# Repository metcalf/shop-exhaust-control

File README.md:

# Shop Exhaust Fan Controller

An ESP32 (ESP-IDF) controller for the woodshop exhaust fan. It runs the fan from particulate sensing and dust collector activity, with local physical controls and Home Assistant reporting. This is the pilot for a Claude-led design process; a dust collector controller follows it.

## Getting started
1. `git init`, then commit this skeleton.
2. Fill in `docs/site-survey.md` (★ items at minimum) and drop photos in `docs/site/`.
3. Answer what you can in `docs/open-questions.md`.
4. Open Claude Code in this directory and say: *"Read CLAUDE.md and STATE.md, then review the site survey and start phase 1."*

Claude follows `CLAUDE.md`: it keeps `STATE.md` current, batches questions, and stops for your approval at each gate (G1–G5).

## Layout
| Path | Purpose |
|------|---------|
| `CLAUDE.md` | Operating instructions for Claude (process, gates, safety rules, conventions) |
| `STATE.md` | Current phase, next actions, blockers |
| `docs/context.md` | Kickoff brief: design thinking already done |
| `docs/site-survey.md` | Your inputs about the shop, fan and preferences |
| `docs/requirements.md` | Requirements with IDs and acceptance criteria |
| `docs/interfaces.md` | I/O, Home Assistant entities, and the shared `DC_RUNNING` interface |
| `docs/decisions.md` | Decision log and gate approvals |
| `docs/open-questions.md` | Batched questions with default assumptions |
| `docs/process-notes.md` | Lessons for the DC project |
| `.claude/agents/` | Subagent definitions: `reviewer` (independent gate reviews), `sourcing` (parts research) |
| `bom.csv` | Bill of materials |
| `firmware/`, `pcb/`, `electrical/`, `mech/`, `reviews/`, `sourcing/` | Created as phases begin |

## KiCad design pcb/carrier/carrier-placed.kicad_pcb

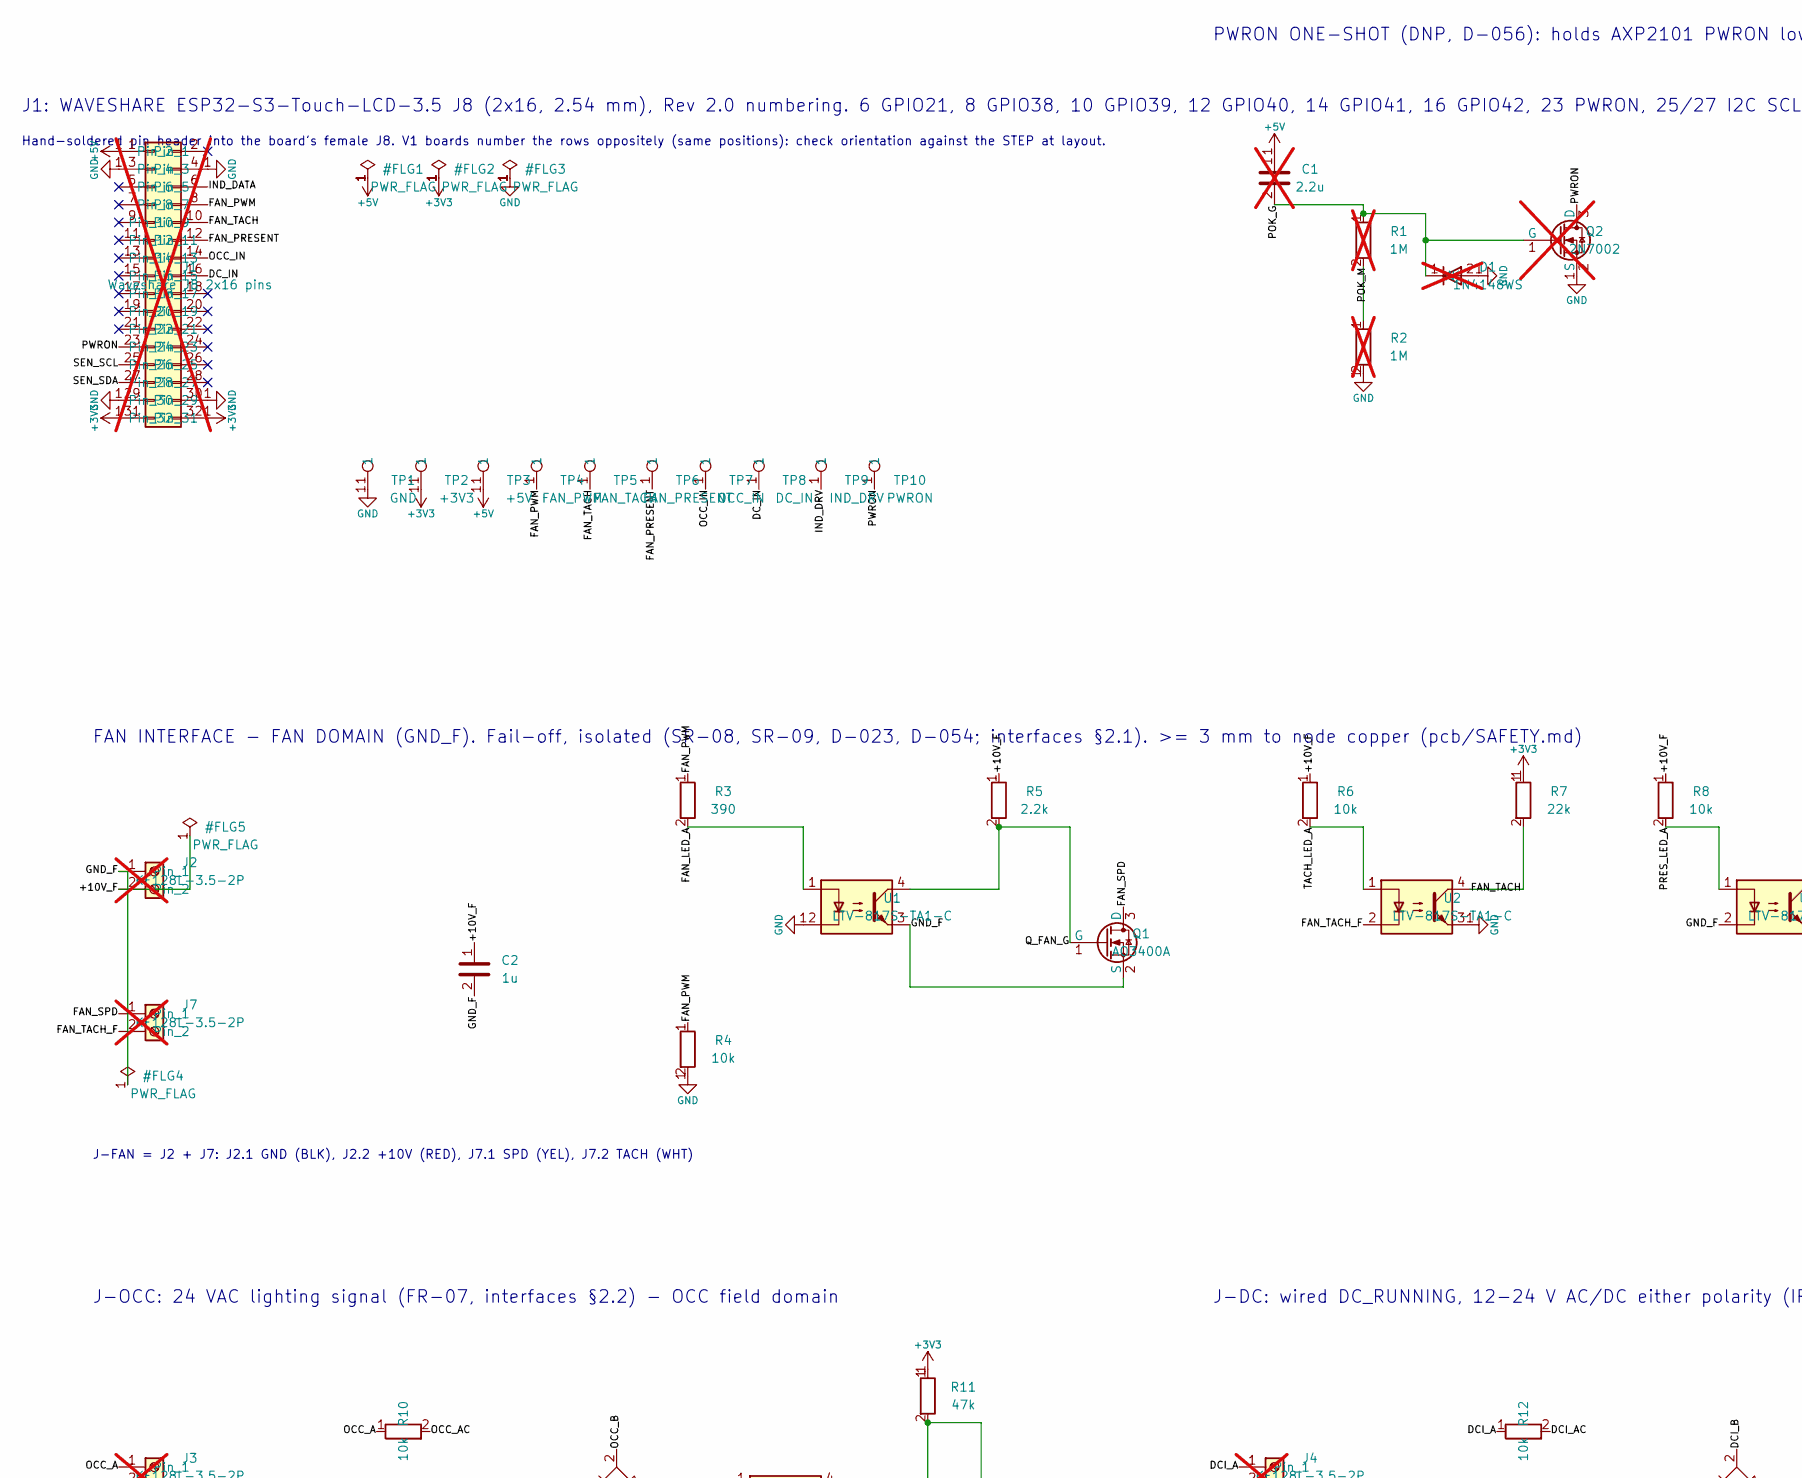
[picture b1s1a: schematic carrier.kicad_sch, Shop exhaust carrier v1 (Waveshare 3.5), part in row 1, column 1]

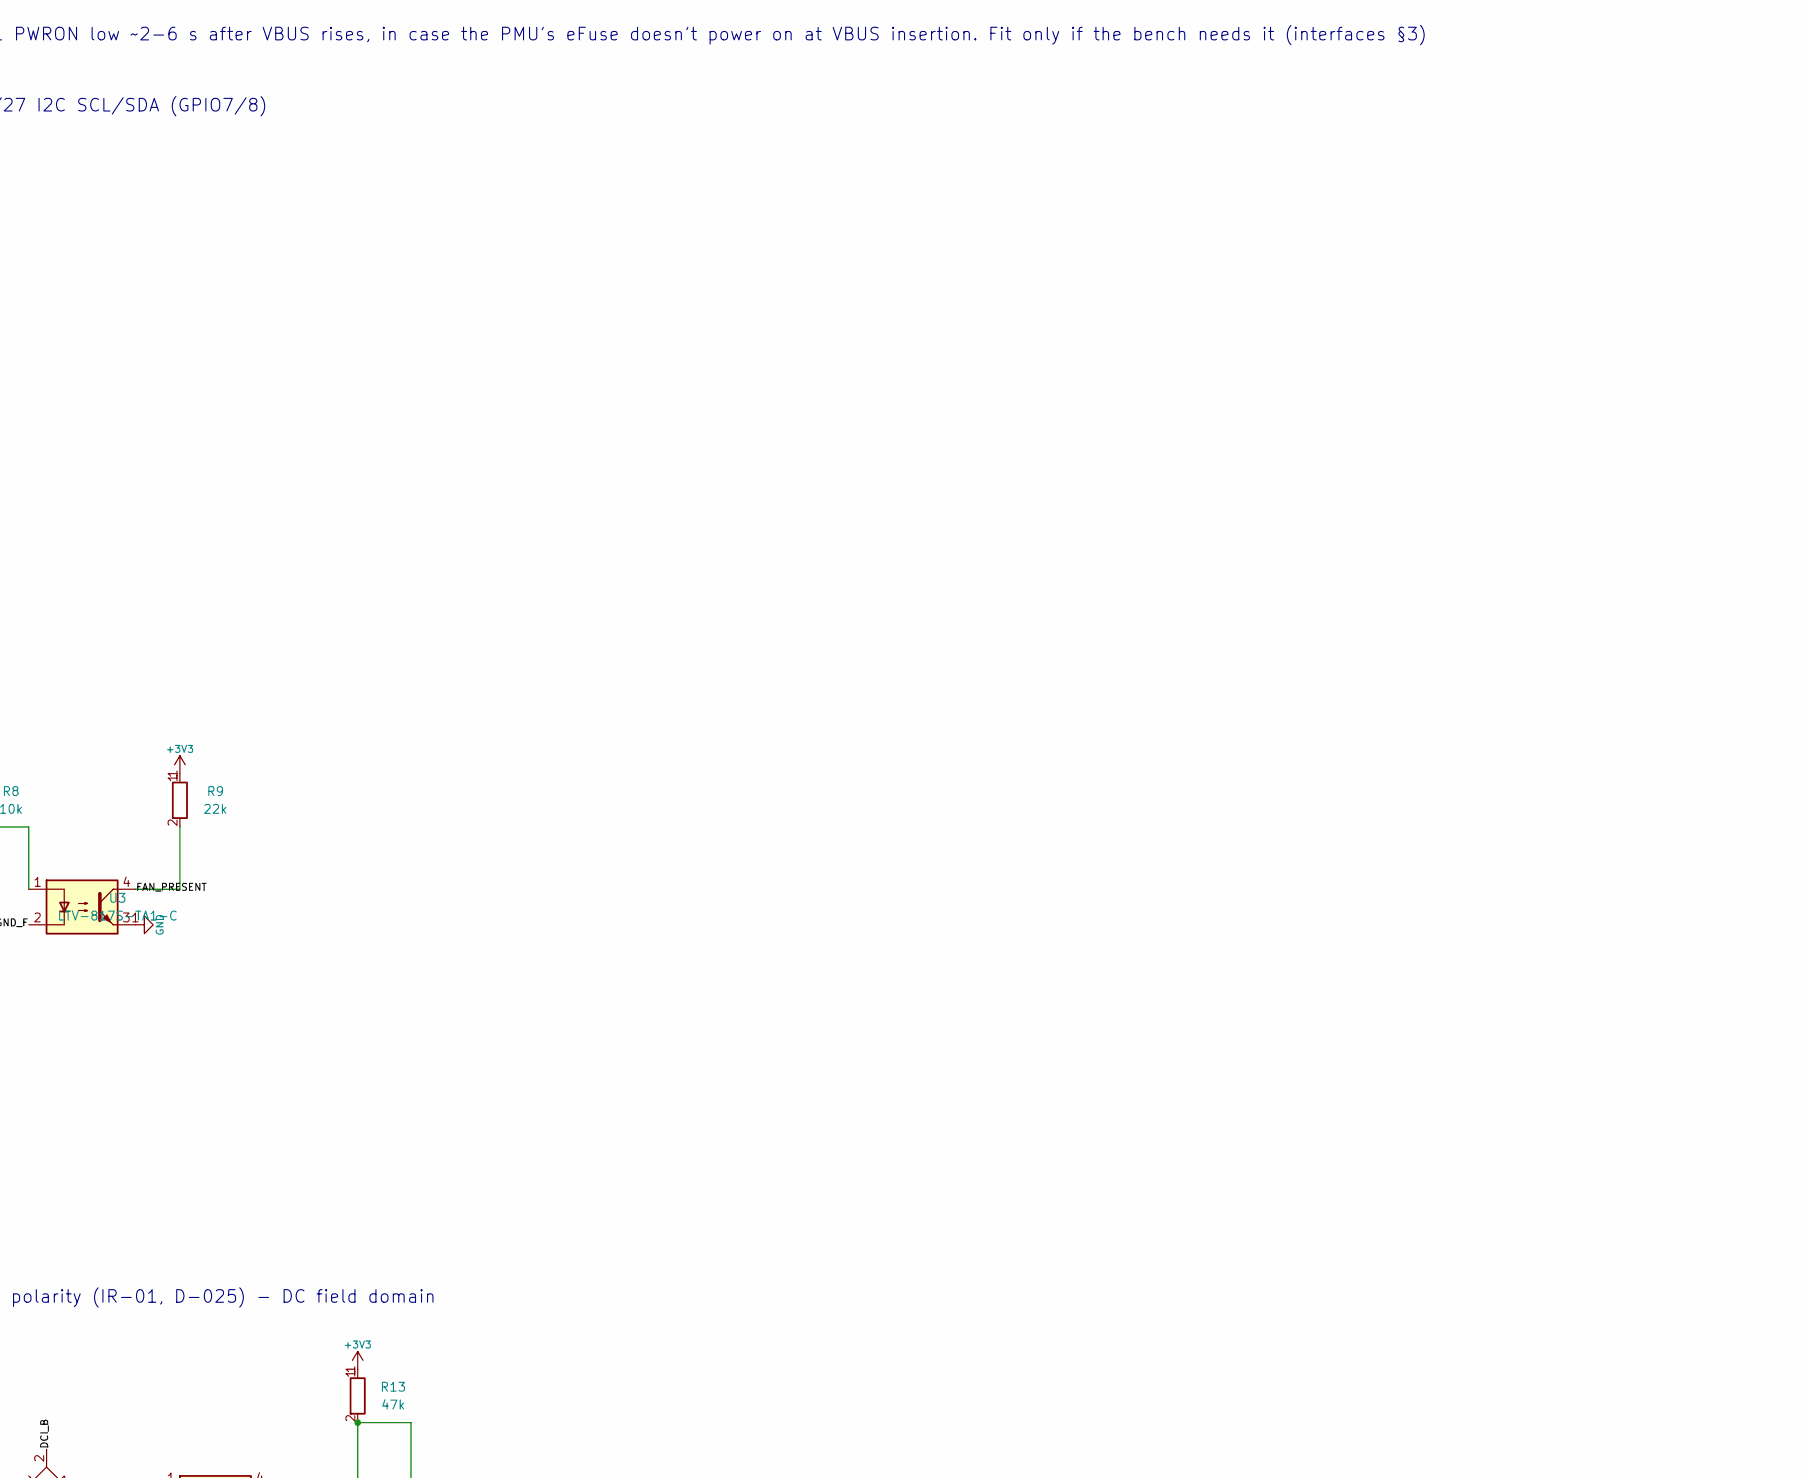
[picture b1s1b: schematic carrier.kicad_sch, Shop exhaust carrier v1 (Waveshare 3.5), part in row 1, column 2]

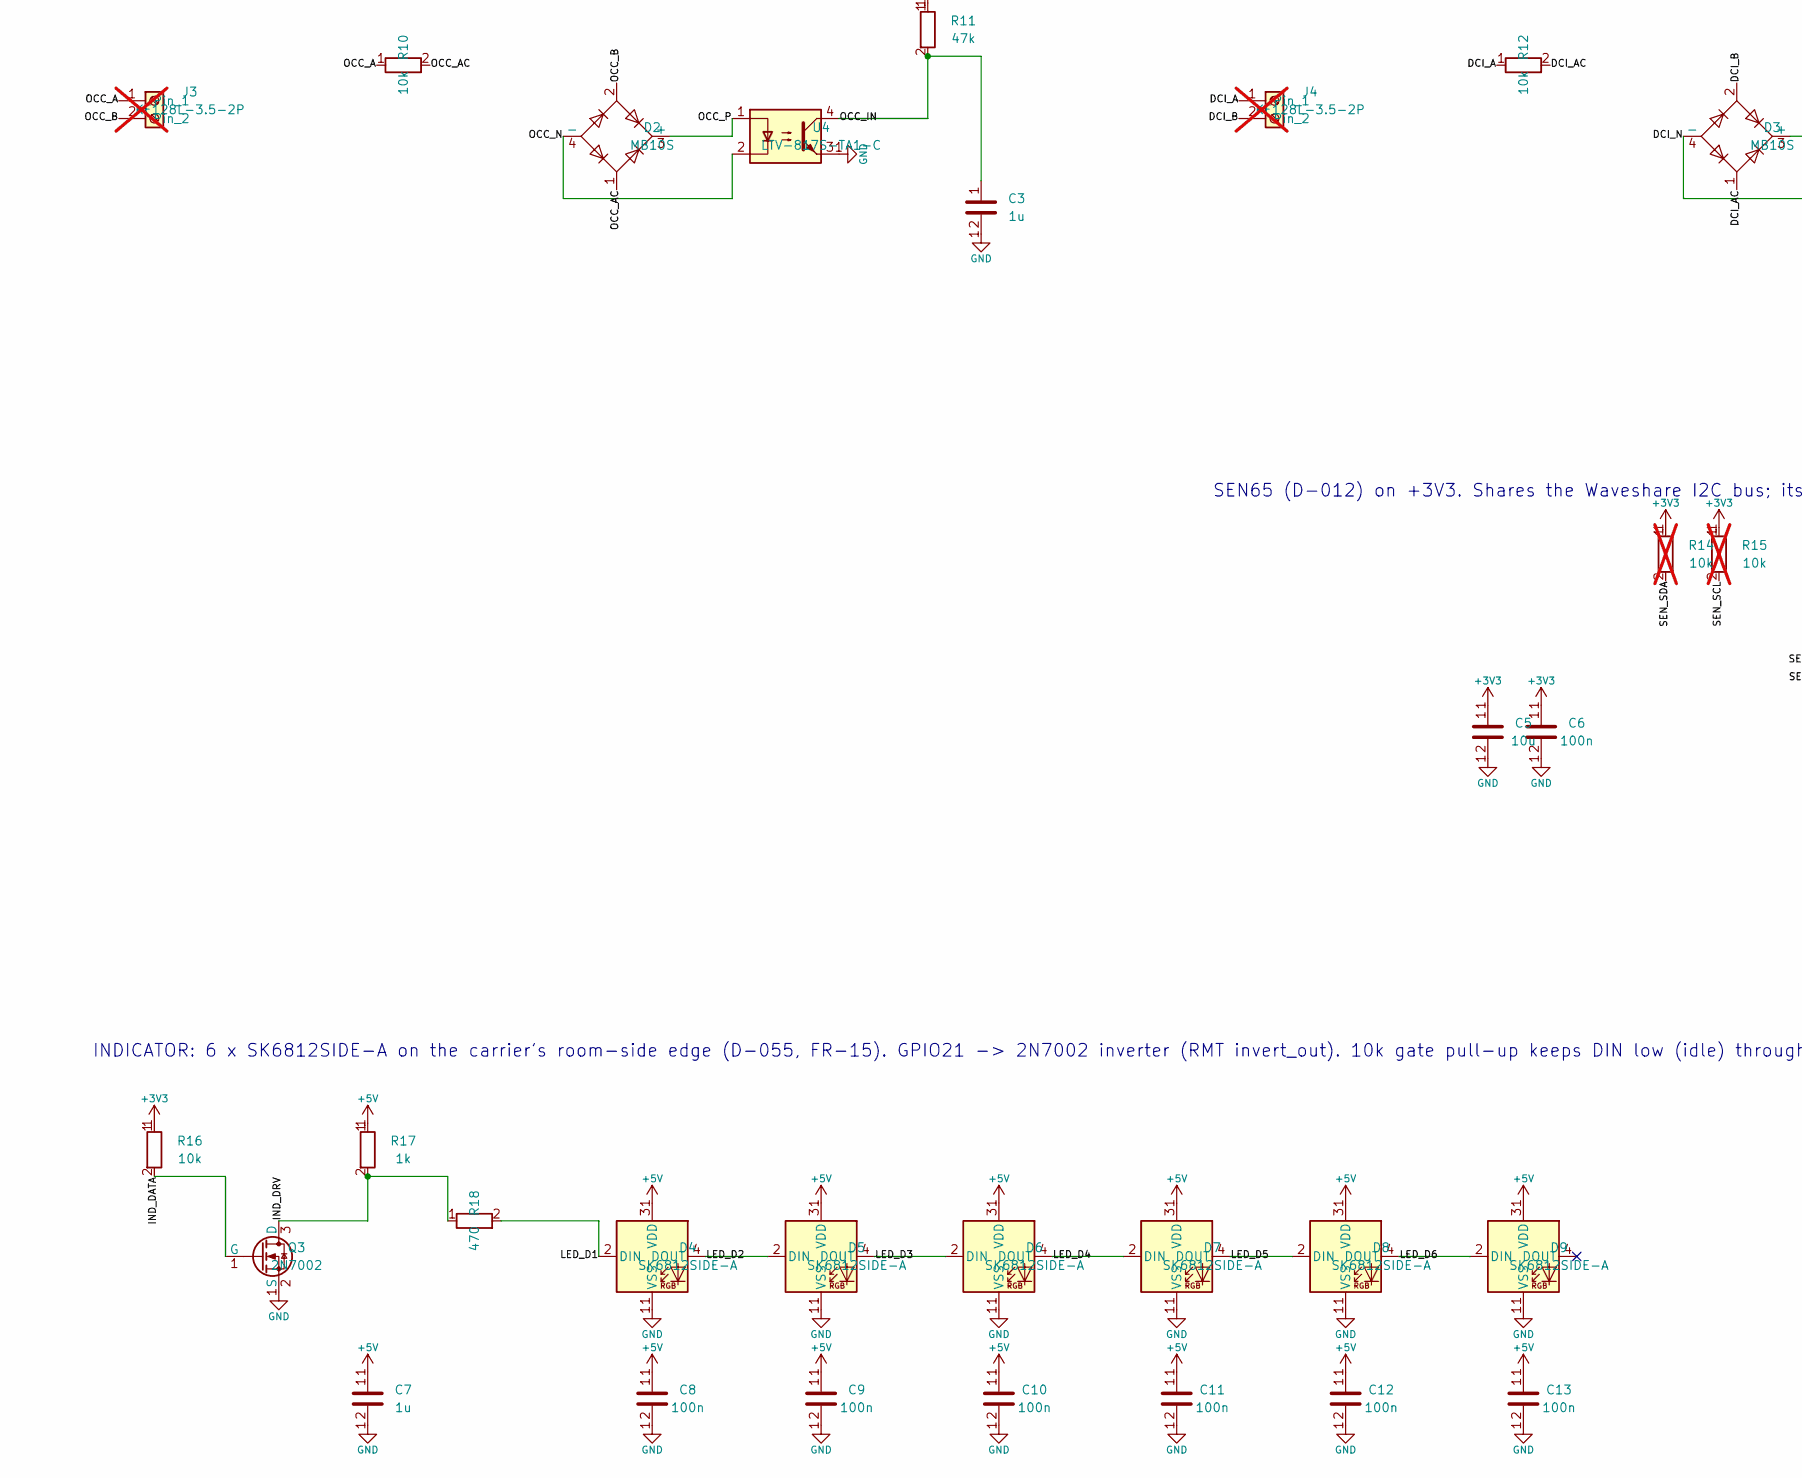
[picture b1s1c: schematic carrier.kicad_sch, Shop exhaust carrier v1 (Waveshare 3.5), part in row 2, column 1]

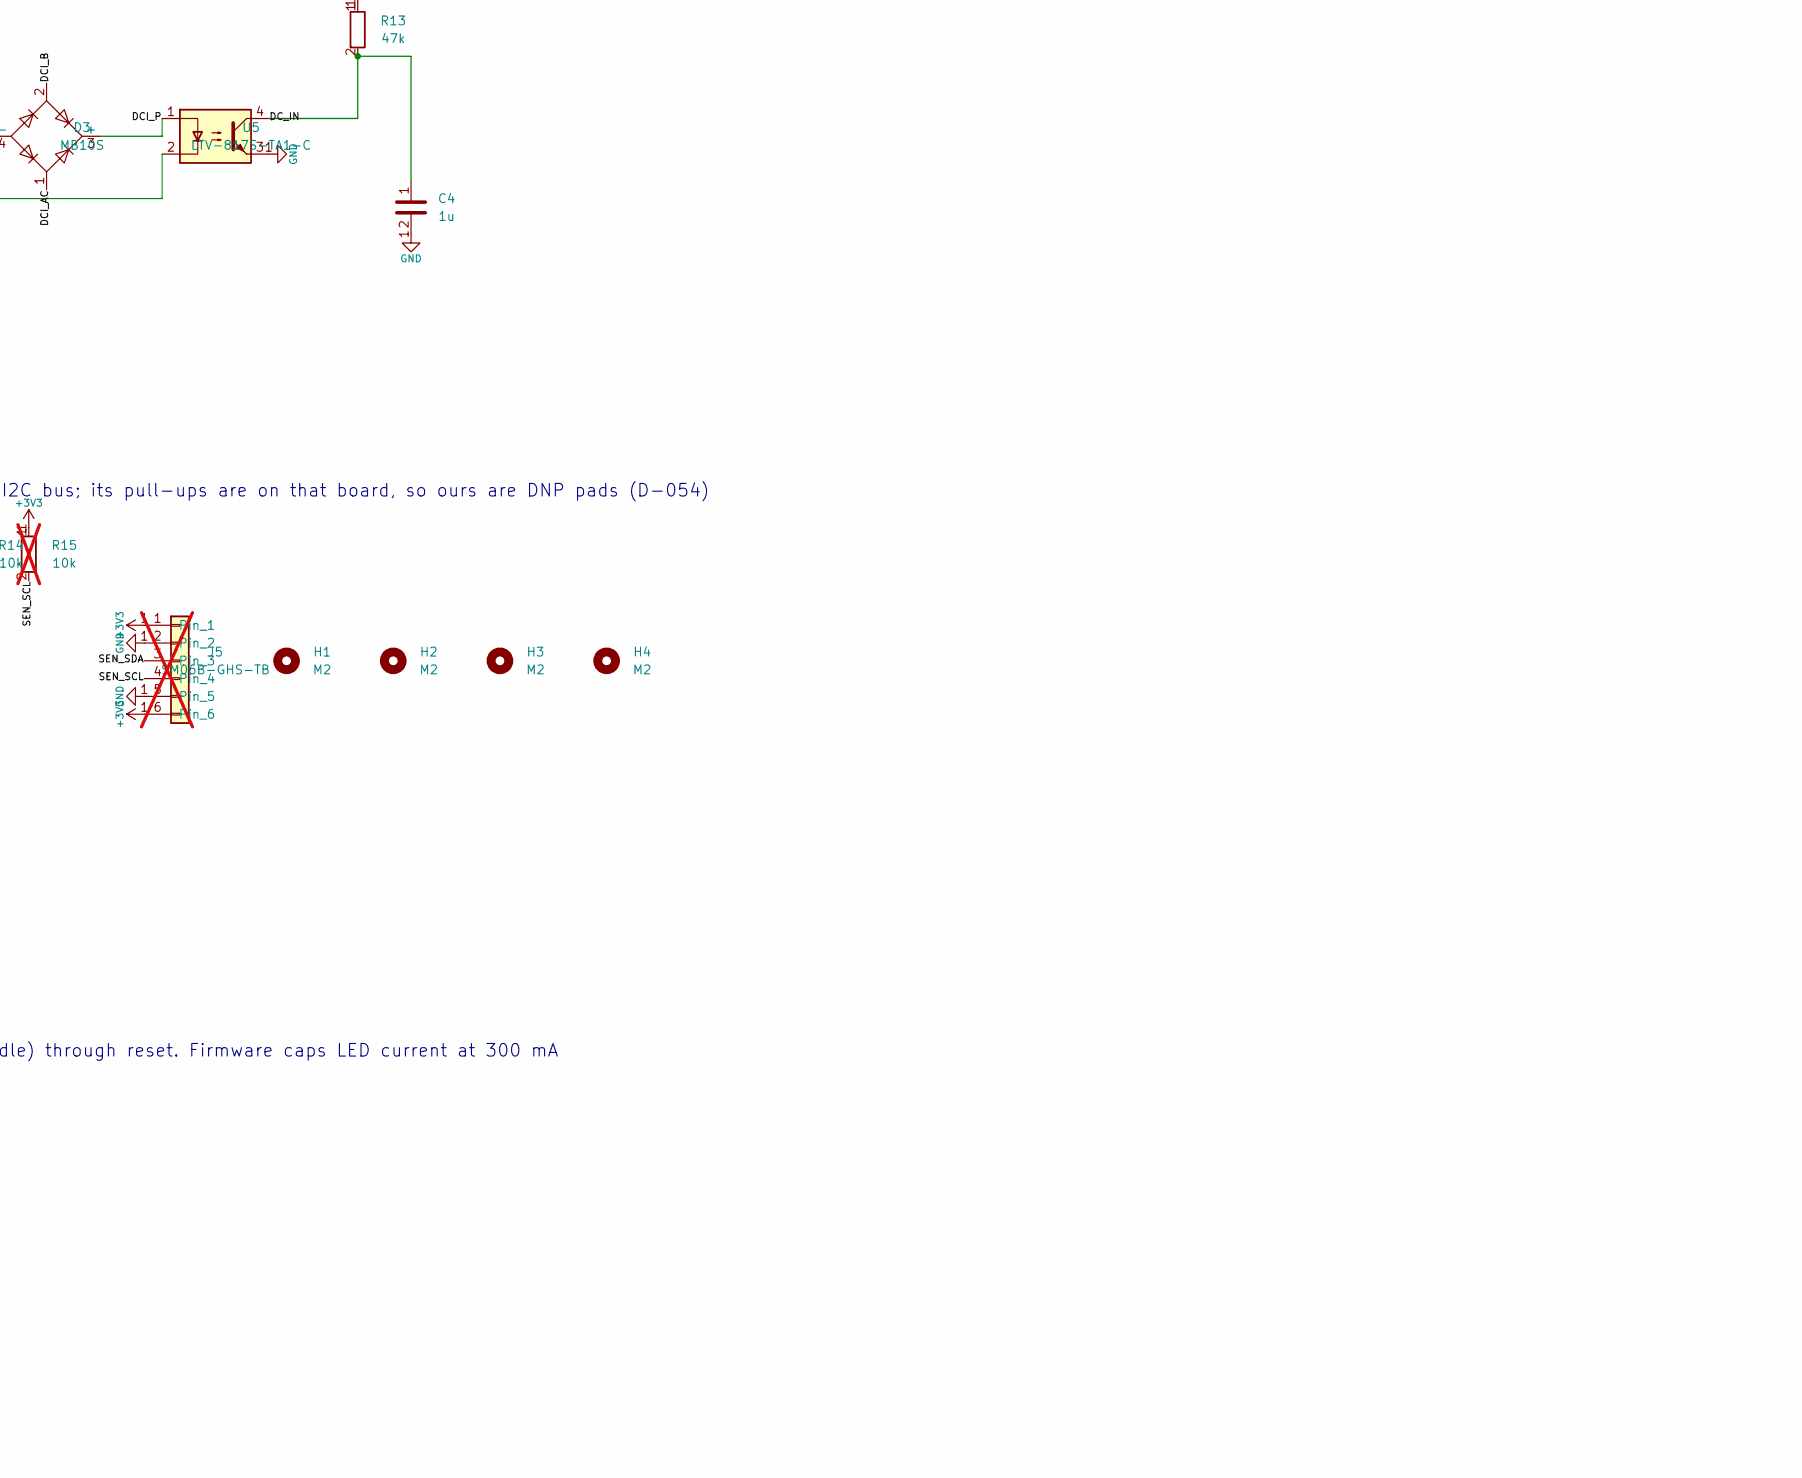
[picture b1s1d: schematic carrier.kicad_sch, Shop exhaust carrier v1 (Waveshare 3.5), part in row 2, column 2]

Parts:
C1: 2.2u; C_0603_1608Metric; not fitted
C2, C3, C4, C7: 1u; C_0603_1608Metric
C5: 10u; C_0805_2012Metric
C6, C8, C9, C10, C11, C12, C13: 100n; C_0603_1608Metric
D1: 1N4148WS; D_SOD-323; LCSC C2128; not fitted
D2, D3: MB10S; Bridge_MBS_MB10S; LCSC C2488
D4, D5, D6, D7, D8, D9: SK6812SIDE-A; LED_SK6812SIDE-A_4.0x1.6mm; LCSC C5378721
H1, H2, H3, H4: M2; MountingHole_2.2mm_M2
J1: Waveshare J8 2x16 pins; PinHeader_2x16_P2.54mm_Vertical; not fitted
J2, J3, J4, J7: KF128L-3.5-2P; TerminalBlock_KF128L-3.5-2P; LCSC C474930; not fitted
J5: SM06B-GHS-TB; JST_GH_SM06B-GHS-TB_1x06-1MP_P1.25mm_Horizontal; LCSC C133065; not fitted
Q1: AO3400A; SOT-23; LCSC C20917
Q2: 2N7002; SOT-23; LCSC C8545; not fitted
Q3: 2N7002; SOT-23; LCSC C8545
R1, R2: 1M; R_0603_1608Metric; not fitted
R3: 390; R_0603_1608Metric
R4, R6, R8, R16: 10k; R_0603_1608Metric
R5: 2.2k; R_0603_1608Metric
R7, R9: 22k; R_0603_1608Metric
R10, R12: 10k; R_1206_3216Metric
R11, R13: 47k; R_0603_1608Metric
R14, R15: 10k; R_0603_1608Metric; not fitted
R17: 1k; R_0603_1608Metric
R18: 470; R_0603_1608Metric
TP1: GND; TestPoint_Pad_D1.5mm
TP2: +3V3; TestPoint_Pad_D1.5mm
TP3: +5V; TestPoint_Pad_D1.5mm
TP4: FAN_PWM; TestPoint_Pad_D1.5mm
TP5: FAN_TACH; TestPoint_Pad_D1.5mm
TP6: FAN_PRESENT; TestPoint_Pad_D1.5mm
TP7: OCC_IN; TestPoint_Pad_D1.5mm
TP8: DC_IN; TestPoint_Pad_D1.5mm
TP9: IND_DRV; TestPoint_Pad_D1.5mm
TP10: PWRON; TestPoint_Pad_D1.5mm
U1, U2, U3, U4, U5: LTV-817S-TA1-C; SOP-4_LTV-817S_LS10.3; LCSC C109227

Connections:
+3V3: C5.1, C6.1, J1.31, J1.32, J5.1, J5.6, R7.1, R9.1, R11.1, R13.1, R14.1, R15.1, R16.1, TP2.1
+5V: C1.1, C7.1, C8.1, C9.1, C10.1, C11.1, C12.1, C13.1, D4.3 (VDD), D5.3 (VDD), D6.3 (VDD), D7.3 (VDD), D8.3 (VDD), D9.3 (VDD), J1.1, R17.1, TP3.1
/+10V_F: C2.1, J2.2, R5.1, R6.1, R8.1
/DCI_A: J4.1, R12.1
/DCI_AC: D3.1, R12.2
/DCI_B: D3.2, J4.2
/DCI_N: D3.4 (-), U5.2
/DCI_P: D3.3 (+), U5.1
/DC_IN: C4.1, J1.16, R13.2, TP8.1, U5.4
/FAN_LED_A: R3.2, U1.1
/FAN_PRESENT: J1.12, R9.2, TP6.1, U3.4
/FAN_PWM: J1.8, R3.1, R4.1, TP4.1
/FAN_SPD: J7.1, Q1.3 (D)
/FAN_TACH: J1.10, R7.2, TP5.1, U2.4
/FAN_TACH_F: J7.2, U2.2
/GND_F: C2.2, J2.1, Q1.2 (S), U1.3, U3.2
/IND_DATA: J1.6, Q3.1 (G), R16.2
/IND_DRV: Q3.3 (D), R17.2, R18.1, TP9.1
/LED_D1: D4.2 (DIN), R18.2
/LED_D2: D4.4 (DOUT), D5.2 (DIN)
/LED_D3: D5.4 (DOUT), D6.2 (DIN)
/LED_D4: D6.4 (DOUT), D7.2 (DIN)
/LED_D5: D7.4 (DOUT), D8.2 (DIN)
/LED_D6: D8.4 (DOUT), D9.2 (DIN)
/OCC_A: J3.1, R10.1
/OCC_AC: D2.1, R10.2
/OCC_B: D2.2, J3.2
/OCC_IN: C3.1, J1.14, R11.2, TP7.1, U4.4
/OCC_N: D2.4 (-), U4.2
/OCC_P: D2.3 (+), U4.1
/POK_G: C1.2, D1.1 (K), Q2.1 (G), R1.1
/POK_M: R1.2, R2.1
/PRES_LED_A: R8.2, U3.1
/PWRON: J1.23, Q2.3 (D), TP10.1
/Q_FAN_G: Q1.1 (G), R5.2, U1.4
/SEN_SCL: J1.25, J5.4, R15.2
/SEN_SDA: J1.27, J5.3, R14.2
/TACH_LED_A: R6.2, U2.1
GND: C3.2, C4.2, C5.2, C6.2, C7.2, C8.2, C9.2, C10.2, C11.2, C12.2, C13.2, D1.2 (A), D4.1 (VSS), D5.1 (VSS), D6.1 (VSS), D7.1 (VSS), D8.1 (VSS), D9.1 (VSS), J1.3, J1.4, J1.29, J1.30, J5.2, J5.5, Q2.2 (S), Q3.2 (S), R2.2, R4.2, TP1.1, U1.2, U2.3, U3.3, U4.3, U5.3

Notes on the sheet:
J1: WAVESHARE ESP32-S3-Touch-LCD-3.5 J8 (2x16, 2.54 mm), Rev 2.0 numbering. 6 GPIO21, 8 GPIO38, 10 GPIO39, 12 GPIO40, 14 GPIO41, 16 GPIO42, 23 PWRON, 25/27 I2C SCL/SDA (GPIO7/8)
Hand-soldered pin header into the board's female J8. V1 boards number the rows oppositely (same positions): check orientation against the STEP at layout.
PWRON ONE-SHOT (DNP, D-056): holds AXP2101 PWRON low ~2-6 s after VBUS rises, in case the PMU's eFuse doesn't power on at VBUS insertion. Fit only if the bench needs it (interfaces §3)
FAN INTERFACE - FAN DOMAIN (GND_F). Fail-off, isolated (SR-08, SR-09, D-023, D-054; interfaces §2.1). >= 3 mm to node copper (pcb/SAFETY.md)
J-FAN = J2 + J7: J2.1 GND (BLK), J2.2 +10V (RED), J7.1 SPD (YEL), J7.2 TACH (WHT)
J-OCC: 24 VAC lighting signal (FR-07, interfaces §2.2) - OCC field domain
J-DC: wired DC_RUNNING, 12-24 V AC/DC either polarity (IR-01, D-025) - DC field domain
SEN65 (D-012) on +3V3. Shares the Waveshare I2C bus; its pull-ups are on that board, so ours are DNP pads (D-054)
INDICATOR: 6 x SK6812SIDE-A on the carrier's room-side edge (D-055, FR-15). GPIO21 -> 2N7002 inverter (RMT invert_out). 10k gate pull-up keeps DIN low (idle) through reset. Firmware caps LED current at 300 mA

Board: 2 copper layers, 68 parts (15 on the bottom side), 39 nets, no tracks yet.

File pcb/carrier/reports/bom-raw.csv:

"Reference","Value","Footprint","LCSC","DNP","QUANTITY"
"C1","2.2u","Capacitor_SMD:C_0603_1608Metric","","DNP","1"
"C2-C4,C7","1u","Capacitor_SMD:C_0603_1608Metric","","","4"
"C5","10u","Capacitor_SMD:C_0805_2012Metric","","","1"
"C6,C8-C13","100n","Capacitor_SMD:C_0603_1608Metric","","","7"
"D1","1N4148WS","Diode_SMD:D_SOD-323","C2128","DNP","1"
"D2,D3","MB10S","exhaust:Bridge_MBS_MB10S","C2488","","2"
"D4-D9","SK6812SIDE-A","carrier:LED_SK6812SIDE-A_4.0x1.6mm","C5378721","","6"
"H1-H4","M2","MountingHole:MountingHole_2.2mm_M2","","","4"
"J1","Waveshare J8 2x16 pins","Connector_PinHeader_2.54mm:PinHeader_2x16_P2.54mm_Vertical","","DNP","1"
"J2-J4,J7","KF128L-3.5-2P","exhaust:TerminalBlock_KF128L-3.5-2P","C474930","DNP","4"
"J5","SM06B-GHS-TB","Connector_JST:JST_GH_SM06B-GHS-TB_1x06-1MP_P1.25mm_Horizontal","C133065","DNP","1"
"Q1","AO3400A","Package_TO_SOT_SMD:SOT-23","C20917","","1"
"Q2","2N7002","Package_TO_SOT_SMD:SOT-23","C8545","DNP","1"
"Q3","2N7002","Package_TO_SOT_SMD:SOT-23","C8545","","1"
"R1,R2","1M","Resistor_SMD:R_0603_1608Metric","","DNP","2"
"R3","390","Resistor_SMD:R_0603_1608Metric","","","1"
"R4,R6,R8,R16","10k","Resistor_SMD:R_0603_1608Metric","","","4"
"R5","2.2k","Resistor_SMD:R_0603_1608Metric","","","1"
"R7,R9","22k","Resistor_SMD:R_0603_1608Metric","","","2"
"R10,R12","10k","Resistor_SMD:R_1206_3216Metric","","","2"
"R11,R13","47k","Resistor_SMD:R_0603_1608Metric","","","2"
"R14,R15","10k","Resistor_SMD:R_0603_1608Metric","","DNP","2"
"R17","1k","Resistor_SMD:R_0603_1608Metric","","","1"
"R18","470","Resistor_SMD:R_0603_1608Metric","","","1"
"TP1","GND","TestPoint:TestPoint_Pad_D1.5mm","","","1"
"TP2","+3V3","TestPoint:TestPoint_Pad_D1.5mm","","","1"
"TP3","+5V","TestPoint:TestPoint_Pad_D1.5mm","","","1"
"TP4","FAN_PWM","TestPoint:TestPoint_Pad_D1.5mm","","","1"
"TP5","FAN_TACH","TestPoint:TestPoint_Pad_D1.5mm","","","1"
"TP6","FAN_PRESENT","TestPoint:TestPoint_Pad_D1.5mm","","","1"
"TP7","OCC_IN","TestPoint:TestPoint_Pad_D1.5mm","","","1"
"TP8","DC_IN","TestPoint:TestPoint_Pad_D1.5mm","","","1"
"TP9","IND_DRV","TestPoint:TestPoint_Pad_D1.5mm","","","1"
"TP10","PWRON","TestPoint:TestPoint_Pad_D1.5mm","","","1"
"U1-U5","LTV-817S-TA1-C","exhaust:SOP-4_LTV-817S_LS10.3","C109227","","5"
